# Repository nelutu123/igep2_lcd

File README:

files needed to create an LCD interface board for the IGEPv2 board.

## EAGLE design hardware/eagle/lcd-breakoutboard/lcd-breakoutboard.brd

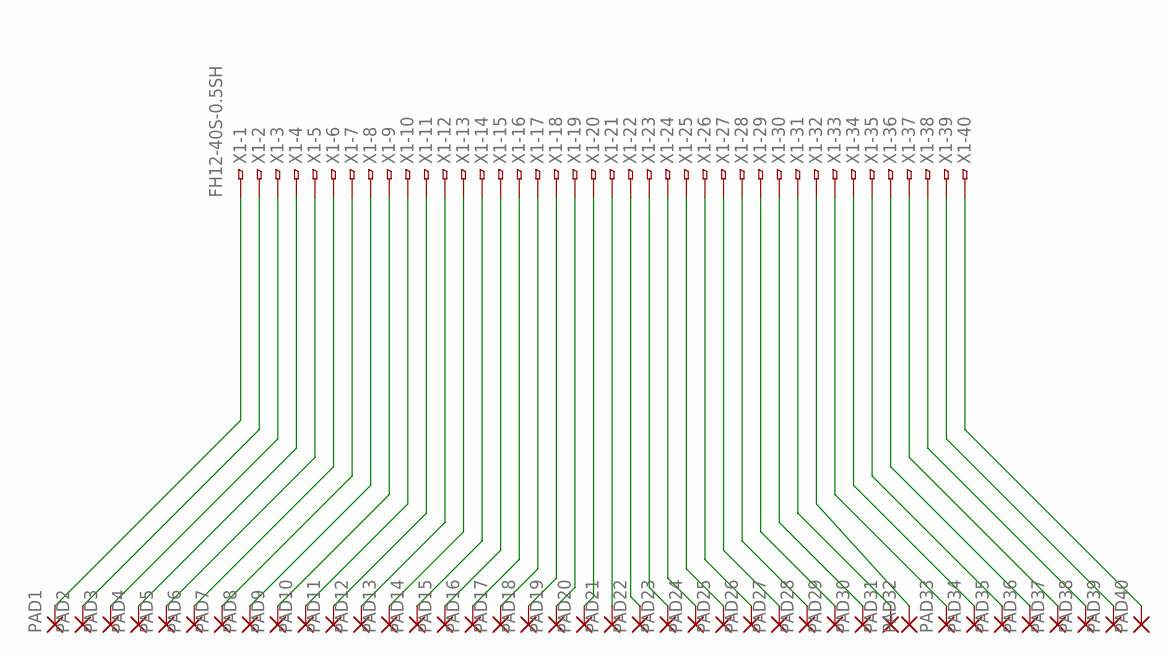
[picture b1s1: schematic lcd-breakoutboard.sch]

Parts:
PAD1, PAD2, PAD3, PAD4, PAD5, PAD6, PAD7, PAD8, PAD9, PAD10, PAD11, PAD12, PAD13, PAD14, PAD15, PAD16, PAD17, PAD18, PAD19, PAD20, PAD21, PAD22, PAD23, PAD24, PAD25, PAD26, PAD27, PAD28, PAD29, PAD30, PAD31, PAD32, PAD33, PAD34, PAD35, PAD36, PAD37, PAD38, PAD39, PAD40: 2,15/1,0
X1: FH12-40S-0.5SH

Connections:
unnamed: PAD1.1, X1.1
unnamed: PAD2.1, X1.2
unnamed: PAD3.1, X1.3
unnamed: PAD4.1, X1.4
unnamed: PAD5.1, X1.5
unnamed: PAD6.1, X1.6
unnamed: PAD7.1, X1.7
unnamed: PAD8.1, X1.8
unnamed: PAD9.1, X1.9
unnamed: PAD10.1, X1.10
unnamed: PAD11.1, X1.11
unnamed: PAD12.1, X1.12
unnamed: PAD13.1, X1.13
unnamed: PAD14.1, X1.14
unnamed: PAD15.1, X1.15
unnamed: PAD16.1, X1.16
unnamed: PAD17.1, X1.17
unnamed: PAD18.1, X1.18
unnamed: PAD19.1, X1.19
unnamed: PAD20.1, X1.20
unnamed: PAD21.1, X1.21
unnamed: PAD22.1, X1.22
unnamed: PAD23.1, X1.23
unnamed: PAD24.1, X1.24
unnamed: PAD25.1, X1.25
unnamed: PAD26.1, X1.26
unnamed: PAD27.1, X1.27
unnamed: PAD28.1, X1.28
unnamed: PAD29.1, X1.29
unnamed: PAD30.1, X1.30
unnamed: PAD31.1, X1.31
unnamed: PAD32.1, X1.32
unnamed: PAD33.1, X1.33
unnamed: PAD34.1, X1.34
unnamed: PAD35.1, X1.35
unnamed: PAD36.1, X1.36
unnamed: PAD37.1, X1.37
unnamed: PAD38.1, X1.38
unnamed: PAD39.1, X1.39
unnamed: PAD40.1, X1.40

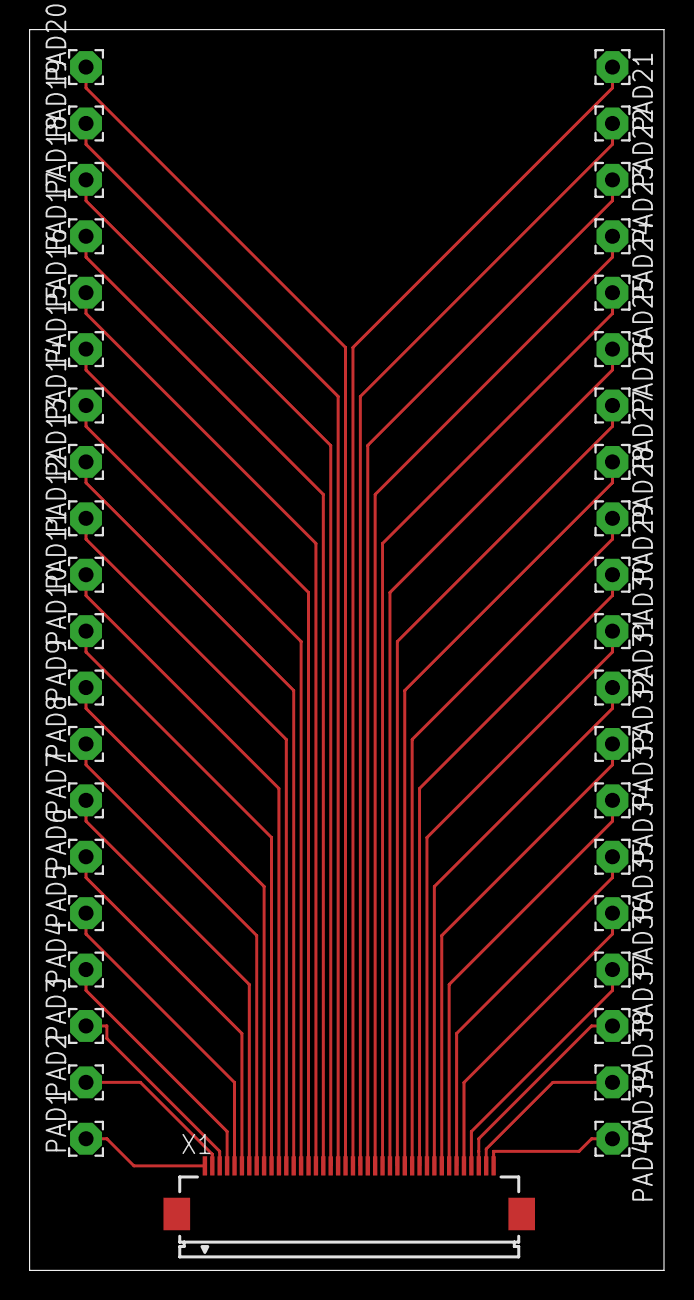
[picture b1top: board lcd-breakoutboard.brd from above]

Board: 2 copper layers, 42.9 x 83.8 mm, 41 parts (0 on the bottom side), 40 nets.

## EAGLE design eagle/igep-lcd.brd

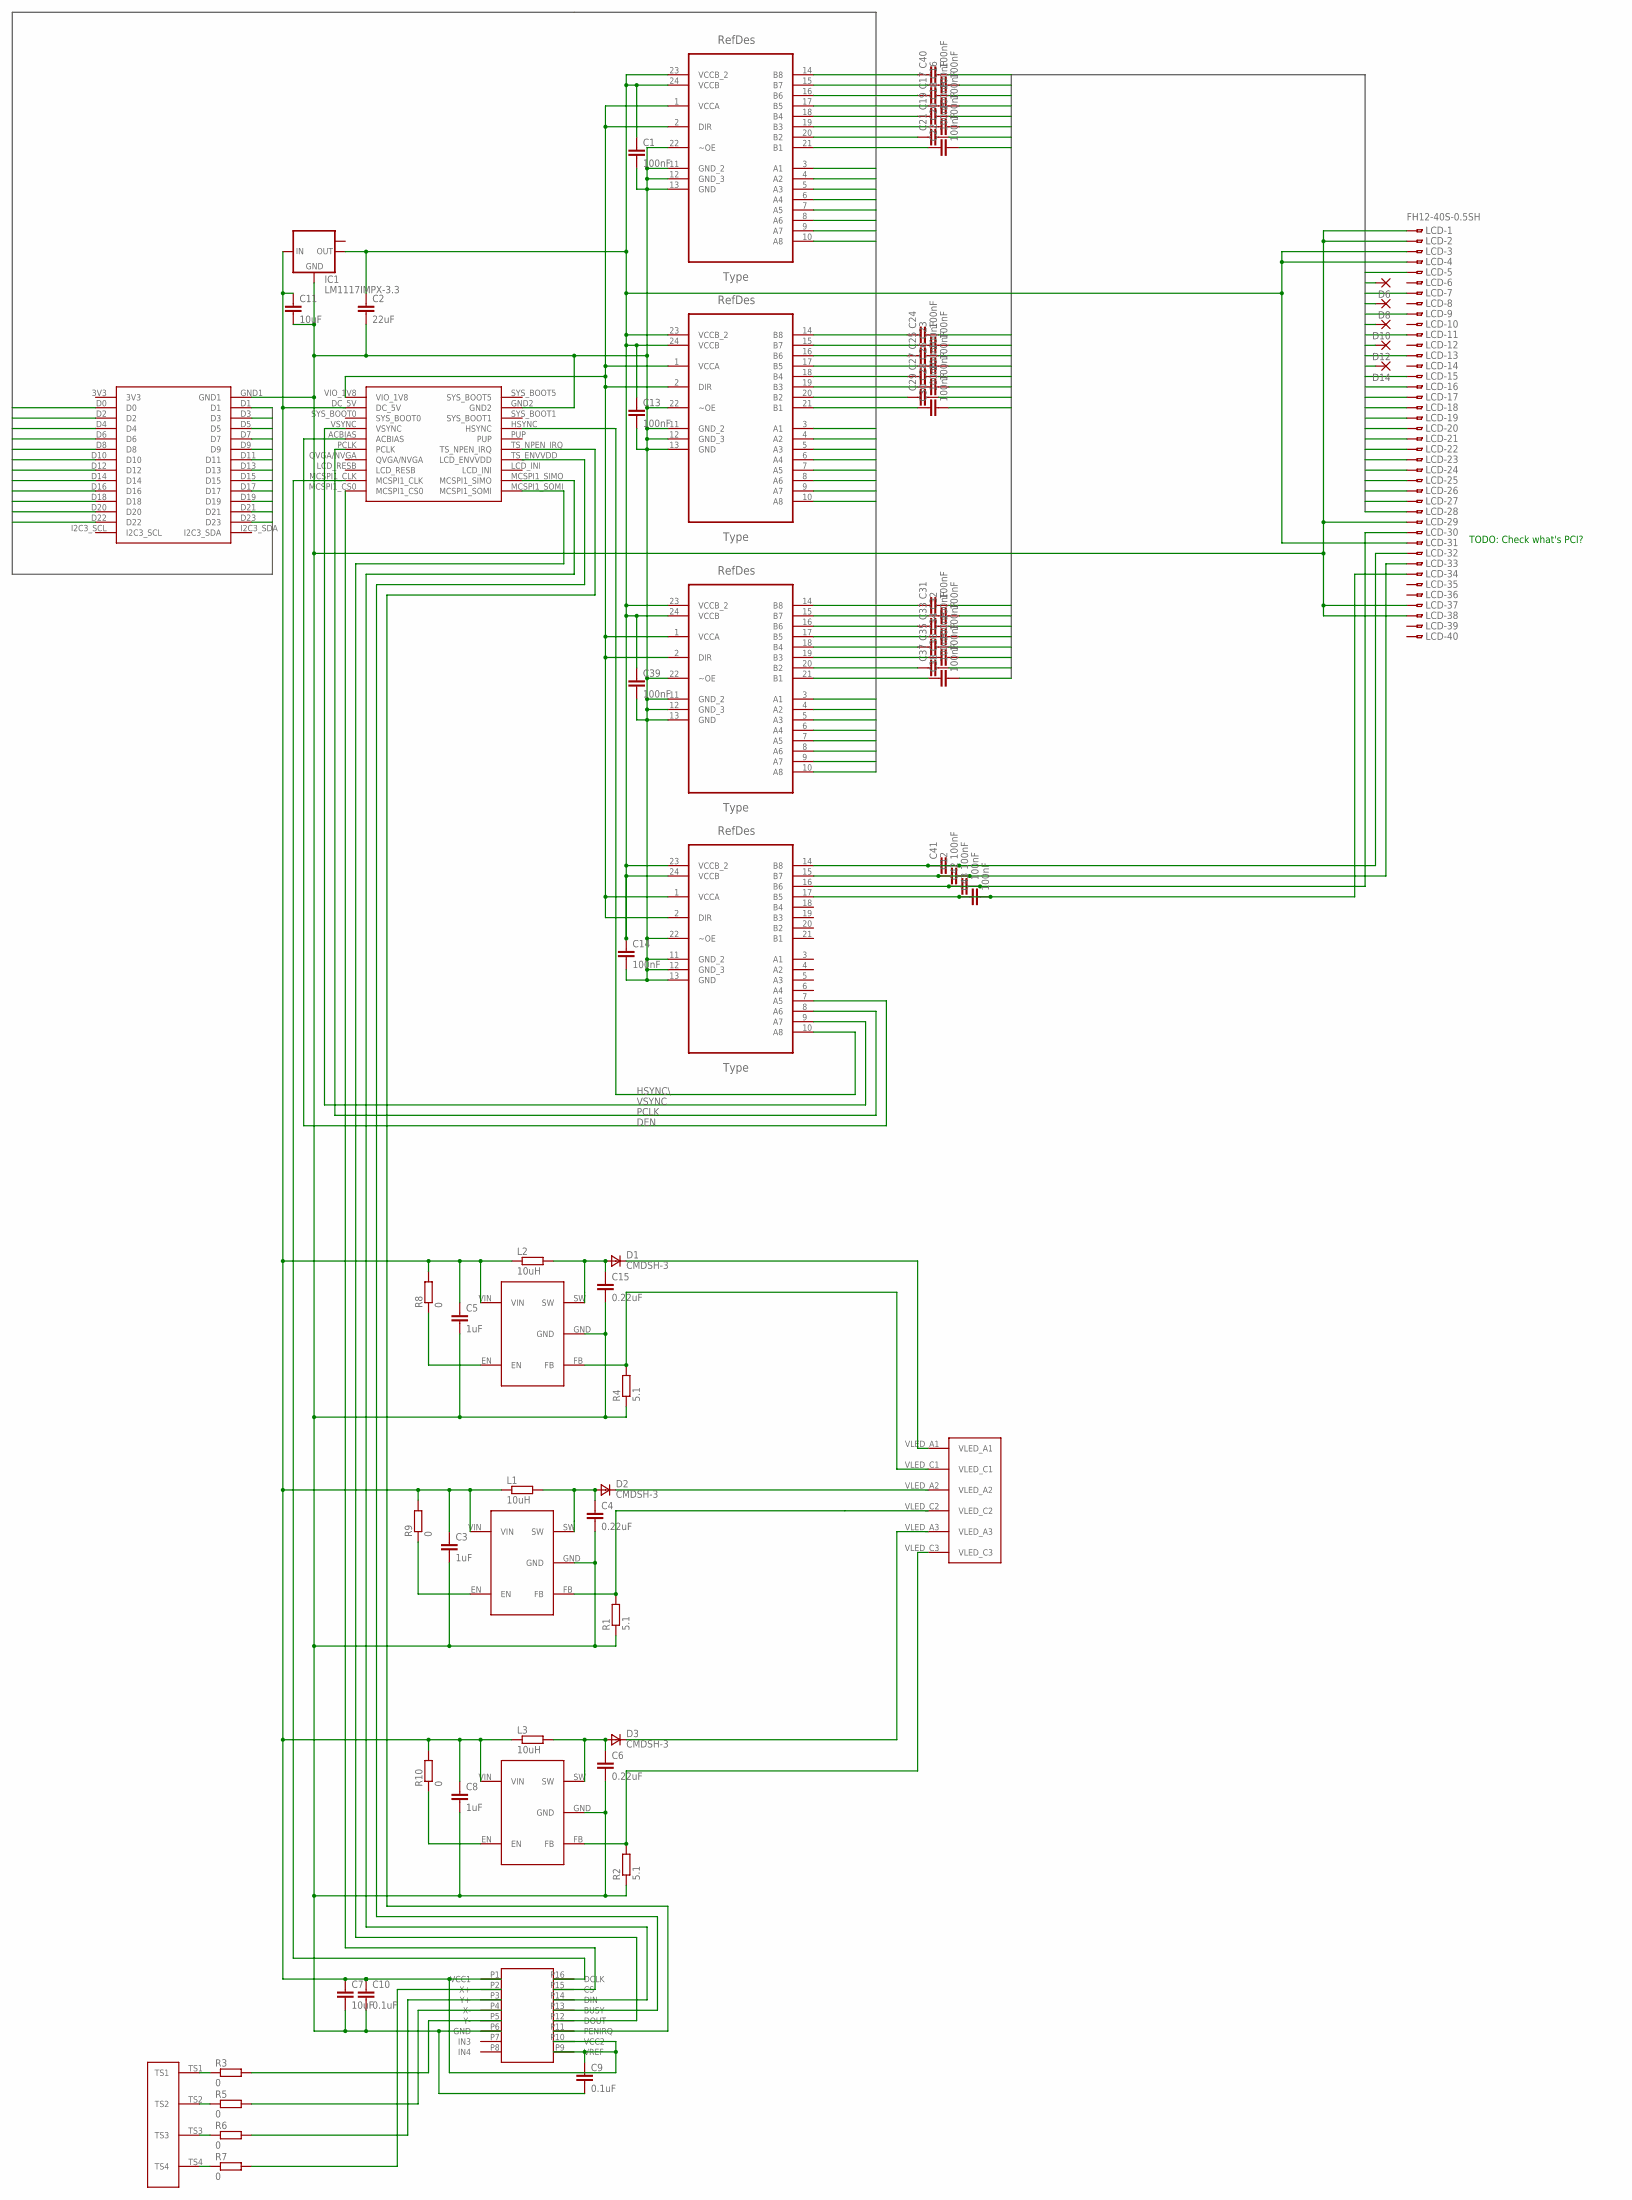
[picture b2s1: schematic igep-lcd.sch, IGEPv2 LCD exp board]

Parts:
C1, C12, C13, C14, C16, C17, C18, C19, C20, C21, C22, C23, C24, C25, C26, C27, C28, C29, C30, C31, C32, C33, C34, C35, C36, C37, C38, C39, C40, C41, C42, C43: 100nF; C1206
C2: 22uF; C1206
C3, C5, C8: 1uF; C1206
C4, C6, C15: 0.22uF; C1206
C7, C11: 10uF; C1206
C9, C10: 0.1uF; C1206
D1, D2, D3: CMDSH-3; SOD323
D6, D8, D10, D12, D14: 1,6/0,8
IC1: LM1117IMPX-3.3; SOT223
L1, L2, L3: 10uH; R1210
LCD: FH12-40S-0.5SH
R1, R2, R4: 5.1; R1206
R3, R5, R6, R7, R8, R9, R10: 0; R1206
U1, U2, U3, U4: SN74LVC8T245PW; SOP65P640X120-24N
U$1: IGEP_LCD
U$2, U$3, U$4: MIC2287
U$5: LCD_BL
U$6: ADS7843
U$7: TS_CON

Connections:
DEN: U4.7 (A5), U$1.ACBIAS
HSYNC\: U4.10 (A8), U$1.HSYNC
IGEP_LCD_DATA0: U1.3 (A1), U$1.D0
IGEP_LCD_DATA1: U1.4 (A2), U$1.D1
IGEP_LCD_DATA2: U1.5 (A3), U$1.D2
IGEP_LCD_DATA3: U1.6 (A4), U$1.D3
IGEP_LCD_DATA4: U1.7 (A5), U$1.D4
IGEP_LCD_DATA5: U1.8 (A6), U$1.D5
IGEP_LCD_DATA6: U1.9 (A7), U$1.D6
IGEP_LCD_DATA7: U1.10 (A8), U$1.D7
IGEP_LCD_DATA8: U2.3 (A1), U$1.D8
IGEP_LCD_DATA9: U2.4 (A2), U$1.D9
IGEP_LCD_DATA10: U2.5 (A3), U$1.D10
IGEP_LCD_DATA11: U2.6 (A4), U$1.D11
IGEP_LCD_DATA12: U2.7 (A5), U$1.D12
IGEP_LCD_DATA13: U2.8 (A6), U$1.D13
IGEP_LCD_DATA14: U2.9 (A7), U$1.D14
IGEP_LCD_DATA15: U2.10 (A8), U$1.D15
IGEP_LCD_DATA16: U3.3 (A1), U$1.D16
IGEP_LCD_DATA17: U3.4 (A2), U$1.D17
IGEP_LCD_DATA18: U3.5 (A3), U$1.D18
IGEP_LCD_DATA19: U3.6 (A4), U$1.D19
IGEP_LCD_DATA20: U3.7 (A5), U$1.D20
IGEP_LCD_DATA21: U3.8 (A6), U$1.D21
IGEP_LCD_DATA22: U3.9 (A7), U$1.D22
IGEP_LCD_DATA23: U3.10 (A8), U$1.D23
LCD_DATA0: C22.2, LCD.21
LCD_DATA1: C21.2, LCD.22
LCD_DATA2: C20.2, LCD.23
LCD_DATA3: C19.2, LCD.24
LCD_DATA4: C18.2, LCD.25
LCD_DATA5: C17.2, LCD.26
LCD_DATA6: C16.2, D6.1, LCD.27
LCD_DATA7: C40.2, LCD.28
LCD_DATA8: C30.2, D8.1, LCD.13
LCD_DATA9: C29.2, LCD.14
LCD_DATA10: C28.2, D10.1, LCD.15
LCD_DATA11: C27.2, LCD.16
LCD_DATA12: C26.2, D12.1, LCD.17
LCD_DATA13: C25.2, LCD.18
LCD_DATA14: C23.2, D14.1, LCD.19
LCD_DATA15: C24.2, LCD.20
LCD_DATA16: C38.2, LCD.5
LCD_DATA17: C37.2, LCD.6
LCD_DATA18: C36.2, LCD.7
LCD_DATA19: C35.2, LCD.8
LCD_DATA20: C34.2, LCD.9
LCD_DATA21: C33.2, LCD.10
LCD_DATA22: C32.2, LCD.11
LCD_DATA23: C31.2, LCD.12
unnamed: U$1.MCSPI1_CLK, U$6.P16 (DCLK)
unnamed: C1.2, C2.2, C3.2, C4.2, C5.2, C6.2, C7.2, C8.2, C9.2, C10.2, C11.2, C13.2, C14.2, C15.2, C39.2, IC1.1 (GND), LCD.1, LCD.2, LCD.29, LCD.37, LCD.38, R1.1, R2.1, R4.1, U1.11 (GND_2), U1.12 (GND_3), U1.13 (GND), U1.22 (~OE), U2.11 (GND_2), U2.12 (GND_3), U2.13 (GND), U2.22 (~OE), U3.11 (GND_2), U3.12 (GND_3), U3.13 (GND), U3.22 (~OE), U4.11 (GND_2), U4.12 (GND_3), U4.13 (GND), U4.22 (~OE), U$1.GND1, U$1.GND2, U$2.GND, U$3.GND, U$4.GND, U$6.P6 (GND)
unnamed: R7.1, U$7.TS4
unnamed: U1.1 (VCCA), U1.2 (DIR), U2.1 (VCCA), U2.2 (DIR), U3.1 (VCCA), U3.2 (DIR), U4.1 (VCCA), U4.2 (DIR), U$1.VIO_1V8
unnamed: C41.1, C41.2, LCD.32, U4.14 (B8)
unnamed: R6.1, U$7.TS3
unnamed: U$1.MCSPI1_CS0, U$6.P15 (CS)
unnamed: C15.1, D1.2 (A), L2.2, U$2.SW
unnamed: C12.1, C12.2, LCD.33, U4.15 (B7)
unnamed: C42.1, C42.2, LCD.30, U4.16 (B6)
unnamed: C43.1, C43.2, LCD.34, U4.17 (B5)
unnamed: R5.1, U$7.TS2
unnamed: D1.1 (C), U$5.VLED_A1
unnamed: R4.2, U$2.FB, U$5.VLED_C1
unnamed: C4.1, D2.2 (A), L1.2, U$3.SW
unnamed: D2.1 (C), U$5.VLED_A2
unnamed: R1.2, U$3.FB, U$5.VLED_C2
unnamed: R3.1, U$7.TS1
unnamed: R10.1, U$4.EN
unnamed: U$1.TS_NPEN_IRQ, U$6.P11 (PENIRQ)
unnamed: C6.1, D3.2 (A), L3.2, U$4.SW
unnamed: D3.1 (C), U$5.VLED_A3
unnamed: R2.2, U$4.FB, U$5.VLED_C3
unnamed: R9.1, U$3.EN
unnamed: U$1.TS_ENVVDD (LCD_ENVVDD), U$6.P13 (BUSY)
unnamed: U$1.MCSPI1_SIMO, U$6.P14 (DIN)
unnamed: U$1.MCSPI1_SOMI, U$6.P12 (DOUT)
unnamed: R8.1, U$2.EN
unnamed: R3.2, U$6.P5 (Y-)
unnamed: C38.1, U3.21 (B1)
unnamed: R5.2, U$6.P4 (X-)
unnamed: C37.1, U3.20 (B2)
unnamed: R6.2, U$6.P3 (Y+)
unnamed: R7.2, U$6.P2 (X+)
unnamed: C3.1, C5.1, C7.1, C8.1, C9.1, C10.1, C11.1, IC1.3 (IN), L1.1, L2.1, L3.1, R8.2, R9.2, R10.2, U$1.DC_5V, U$2.VIN, U$3.VIN, U$4.VIN, U$6.P1 (VCC1), U$6.P9 (VREF), U$6.P10 (VCC2)
unnamed: C1.1, C2.1, C13.1, C14.1, C39.1, IC1.2 (OUT), LCD.3, LCD.4, LCD.31, U1.23 (VCCB_2), U1.24 (VCCB), U2.23 (VCCB_2), U2.24 (VCCB), U3.23 (VCCB_2), U3.24 (VCCB), U4.23 (VCCB_2), U4.24 (VCCB)
unnamed: C36.1, U3.19 (B3)
unnamed: C35.1, U3.18 (B4)
unnamed: C34.1, U3.17 (B5)
unnamed: C33.1, U3.16 (B6)
unnamed: C32.1, U3.15 (B7)
unnamed: C31.1, U3.14 (B8)
unnamed: C30.1, U2.21 (B1)
unnamed: C29.1, U2.20 (B2)
unnamed: C28.1, U2.19 (B3)
unnamed: C27.1, U2.18 (B4)
unnamed: C26.1, U2.17 (B5)
unnamed: C25.1, U2.16 (B6)
unnamed: C23.1, U2.15 (B7)
unnamed: C24.1, U2.14 (B8)
unnamed: C22.1, U1.21 (B1)
unnamed: C21.1, U1.20 (B2)
unnamed: C20.1, U1.19 (B3)
unnamed: C19.1, U1.18 (B4)
unnamed: C18.1, U1.17 (B5)
unnamed: C17.1, U1.16 (B6)
unnamed: C16.1, U1.15 (B7)
unnamed: C40.1, U1.14 (B8)
PCLK: U4.8 (A6), U$1.PCLK
VSYNC: U4.9 (A7), U$1.VSYNC

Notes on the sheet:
TODO: Check what's PCI?

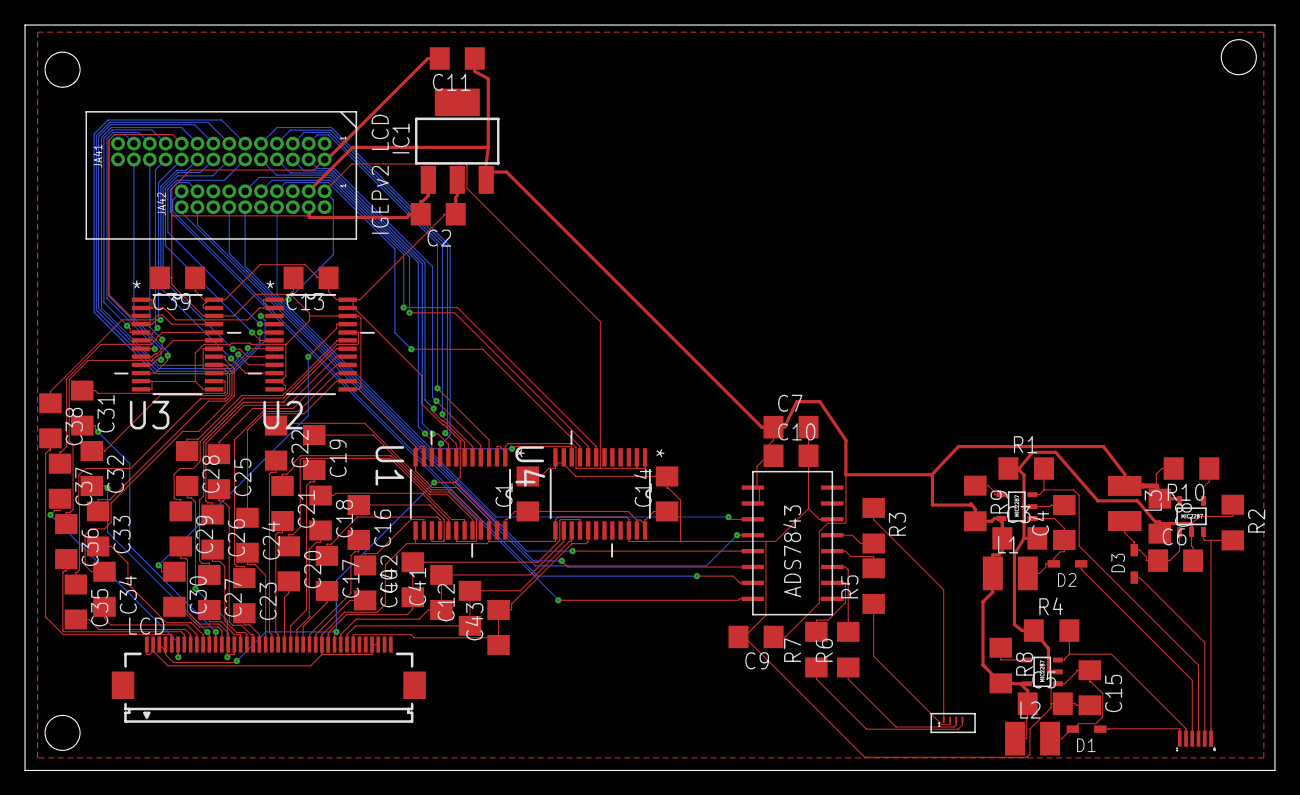
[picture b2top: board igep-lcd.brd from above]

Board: 2 copper layers, 99.9 x 59.6 mm, 72 parts (0 on the bottom side), 110 nets.

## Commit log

2011-11-24 initial
2011-11-24 added igep2 specs
2011-12-21 minor
2011-12-21 Added igep-lcd connector eagle library Added igep hardware manual
2011-12-21 Added LCD spec
2012-01-17 Added level shifters + voltage regulator
2012-01-17 Added LCD data bus to level shifters
2012-01-17 Igep lcd data to level shifters
2012-01-17 Added all LCD data lines and clocks
2012-01-17 Added components list
2012-01-17 Updated components list
2012-01-30 Added documentation LED driver
2012-01-30 Add mic2287 eagle library
2012-01-30 Added datasheet for touchscreen digitizer.
2012-01-30 Added LCD backlight driver (lacking the connector)
2012-01-31 Changed PCB layout, added text
2012-01-31 Added all backlight controllers.
2012-01-31 Design rules, satland
2012-01-31 Added Farnell codes for D1, D2 and D3
2012-01-31 Added backlight connectors
2012-01-31 Freerouting script
2012-01-31 Updated components list. Added proper datasheet for touchscreen digitizer.
2012-03-06 Add ADS7843 (touchscreen) eagle library
2012-03-17 Added touchscreen digitizer. TODO: touchscreen connector missing.
2012-04-03 Changed some components packages
2012-04-03 Replaced all RLC elements with SMD packages
2012-04-03 Fixed one forgotten capacitor
2012-04-03 Added the headers
2012-04-03 Added TS connector eagle library Added TS connector to the schematic
2012-04-03 Added lcd connector Fix connections @ schema
2012-04-03 Fixed ERC rules for bus
2012-04-06 Added crosslinks on decoupling capacitors (to ease prototyping)
2012-04-06 Added name on package
2012-04-06 Minor fixes
2012-04-06 Started with schematics design
2012-04-06 Developing PCB design...
2012-04-06 First phase of PCD design
2012-04-06 First routed version of the PCB
2012-04-06 PCB layout phase 2 done
2012-04-06 Added eagle ignores
2012-04-06 Updated schematics
2012-04-06 Added routing + ground plates + holes
2012-04-06 Wider power lines for LCD backlight
2012-04-06 Final PCB design, first version
2012-04-06 Add files for satland
2012-04-06 Added job files, rev1
2012-04-11 added howto.txt
2012-05-08 all components received from Farnell
2012-06-04 Added workaround for different design rules
2012-06-04 Added routing
2012-06-05 Added correct dru
2012-06-05 Revert to 286b264bb1132dfa6f59ae8d288566ef804c77dd
2012-06-05 Added correct design rules
2012-06-05 Fixed postion testpads in schematic
2012-06-20 Created hardware / software dirs Added hello world kernel module
2012-06-21 added BeagleBone docs
2012-06-21 added beaglebone processor docs
2012-06-21 Added lcd breakout board design
2012-06-21 Added cam files lcd breakout board (rev 1)
2012-10-26 Added arm-cortex_a8 64 bit toolchain, built with crosstool-ng
